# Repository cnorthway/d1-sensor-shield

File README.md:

# Wemos D1 Mini Sensor Shield

```
Note: This design was built using KiCad Nightly, and will only open in KiCad Nightly
```

To be used for a series of workshops given by the
Northeastern University Wireless Club.

Intended to be stacked on top of a Wemos D1 Mini. Contains temperature sensor,
photocell, SPI flash, and status LEDs.

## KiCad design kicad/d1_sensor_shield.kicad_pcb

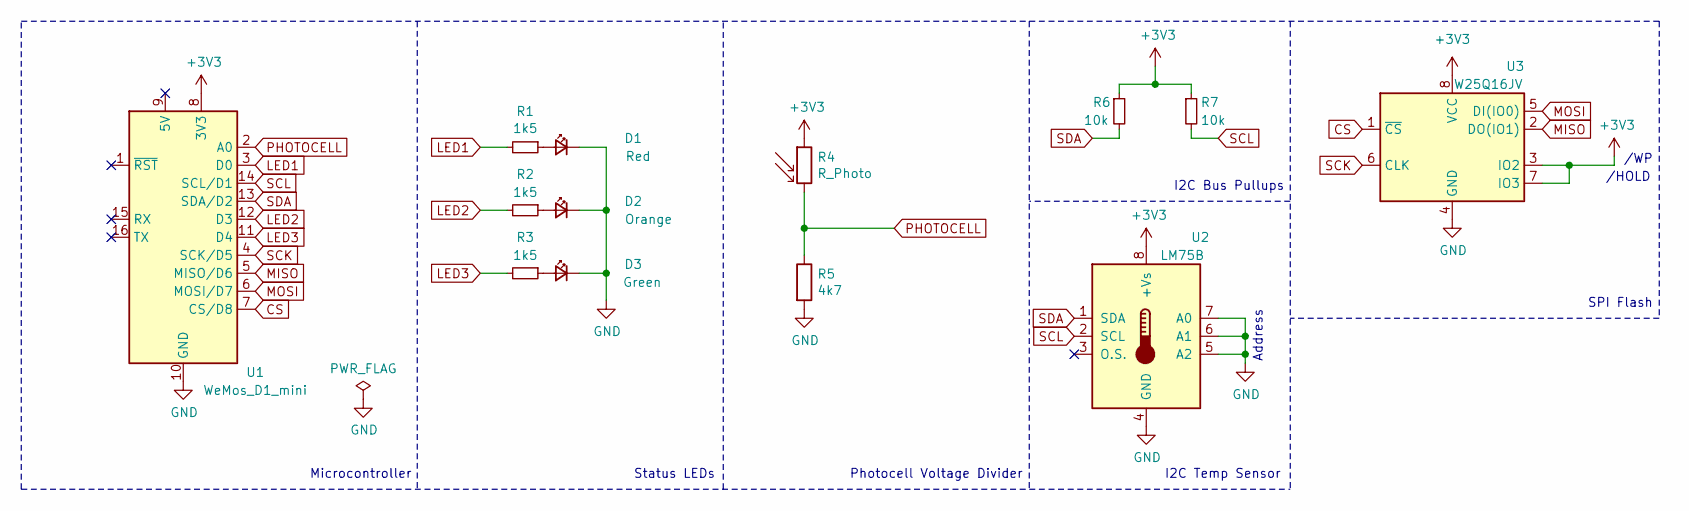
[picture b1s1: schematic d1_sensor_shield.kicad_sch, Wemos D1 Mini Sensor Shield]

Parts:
D1: Red; LED_0805_2012Metric_Pad1.15x1.40mm_HandSolder
D2: Orange; LED_0805_2012Metric_Pad1.15x1.40mm_HandSolder
D3: Green; LED_0805_2012Metric_Pad1.15x1.40mm_HandSolder
R1, R2, R3: 1k5; R_1206_3216Metric_Pad1.30x1.75mm_HandSolder
R4: R_Photo; R_LDR_5.1x4.3mm_P3.4mm_Vertical
R5: 4k7; R_1206_3216Metric_Pad1.30x1.75mm_HandSolder
R6, R7: 10k; R_1206_3216Metric_Pad1.30x1.75mm_HandSolder
U1: WeMos_D1_mini; WEMOS_D1_mini_light
U2: LM75B; SOIC-8_3.9x4.9mm_P1.27mm
U3: W25Q16JV; SOIC-8_5.23x5.23mm_P1.27mm

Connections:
+3V3: R4.1, R6.1, R7.1, U1.8 (3V3), U2.8 (+Vs), U3.3 (IO2), U3.7 (IO3), U3.8 (VCC)
CS: U1.7 (CS/D8), U3.1 (~CS)
GND: D1.1 (K), D2.1 (K), D3.1 (K), R5.2, U1.10 (GND), U2.4 (GND), U2.5 (A2), U2.6 (A1), U2.7 (A0), U3.4 (GND)
LED1: R1.2, U1.3 (D0)
LED2: R2.2, U1.12 (D3)
LED3: R3.2, U1.11 (D4)
MISO: U1.5 (MISO/D6), U3.2 (DO(IO1))
MOSI: U1.6 (MOSI/D7), U3.5 (DI(IO0))
unnamed: D1.2 (A), R1.1
unnamed: D2.2 (A), R2.1
unnamed: D3.2 (A), R3.1
PHOTOCELL: R4.2, R5.1, U1.2 (A0)
SCK: U1.4 (SCK/D5), U3.6 (CLK)
SCL: R7.2, U1.14 (SCL/D1), U2.2 (SCL)
SDA: R6.2, U1.13 (SDA/D2), U2.1 (SDA)

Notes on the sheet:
Microcontroller
Status LEDs
Photocell Voltage Divider
I2C Temp Sensor
I2C Bus Pullups
Address
SPI Flash
/HOLD
/WP

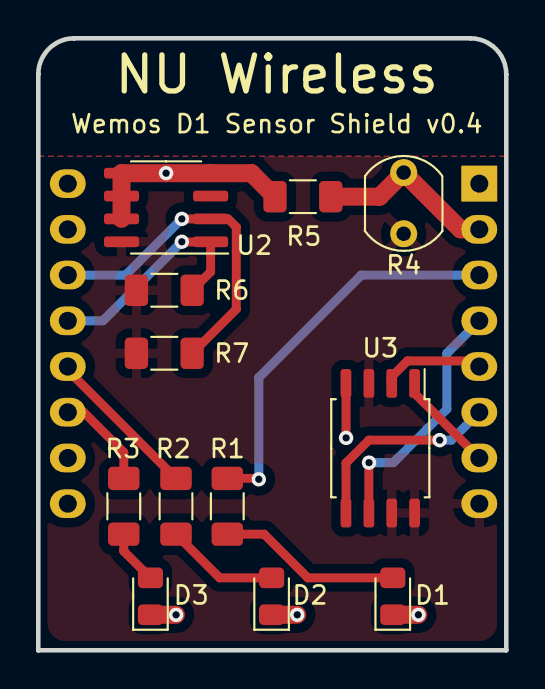
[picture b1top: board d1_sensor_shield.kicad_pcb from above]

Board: 2 copper layers, 26.0 x 34.0 mm, 13 parts (1 on the bottom side), 15 nets.

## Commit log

2021-01-08 Add README
2021-01-09 remove layer alignment target
2021-01-09 Flip D1 to other side of board
    Wemos D1 footprint was incorrectly placed
2021-01-11 add CERN OHL-P V2 license
    open hardware is cool!
2021-01-12 Redo edge cuts in 10mil thickness, move silkscreen
    also shift oshw logo
2021-02-14 Update SPI flash footprint, silkscreen
2021-02-23 widen photocell footprint
2021-02-23 v0.4, change size slightly
2021-02-25 add manufacturing files v0.4
2021-03-04 add interactive BOM file
2021-04-13 Add note about KiCad Nightly
2021-04-13 Update render screenshots
